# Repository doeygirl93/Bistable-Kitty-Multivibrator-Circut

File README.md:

# Bistable Kitty Multivibrator
###### TOTAL TIME: 3hr 21min
Hackatime: https://lapse.hackclub.com/timelapse/kpVtzk44xacg

This is a PCB for a Bistable multivibrator. I made it cause we were forced to in Reslution hardware week 2. But I choose this spefic circut because I liked how there are only 2 states and it could be useful for many other circuts like analog so I thought this would be a useful on to pratice

DEMO LINKS:
Schematic:
https://kicanvas.org/?repo=https://github.com/doeygirl93/Bistable-Kitty-Multivibrator-Circut/blob/main/src/Kicad/Bistable%20Multivibrator.kicad_sch
PCB:
https://kicanvas.org/?repo=https://github.com/doeygirl93/Bistable-Kitty-Multivibrator-Circut/blob/main/src/Kicad/Bistable%20Multivibrator.kicad_pcb
---

## Simulation

So this works like a flipflop. SO this type of circut only has 2 stable states and it always remains inside on the state until you physically switch to another. And while one is on the other has to be off. In context of digital circuts it can be used as basic memory elements. And i used 6 resitors, 2 led 2 npn transitoris 2 switches.

[Link to Demo]($ 1 0.000005 10.20027730826997 50 5 50 5e-11
R 512 160 480 160 0 0 40 5 0 0 0.5
w 512 160 592 160 0
162 592 256 528 256 2 default-led 1 0 0 0.01
g 528 256 528 272 0 0
w 592 256 592 304 0
t 656 320 592 320 0 1 -0.3882099641741541 0.6902026669380696 100 default
g 592 336 592 384 0 0
w 704 256 816 304 0
w 656 320 816 256 0
w 592 160 912 160 0
162 912 240 992 240 2 default-led 1 0 0 0.01
g 992 240 992 288 0 0
s 656 432 576 432 0 1 false
R 576 432 544 368 0 0 40 5 0 0 0.5
w 912 240 912 288 0
t 880 304 912 304 0 1 -0.38820996417420517 0.6902026669380692 100 default
w 816 304 880 304 0
s 816 416 880 416 0 1 false
R 880 416 880 368 0 0 40 5 0 0 0.5
g 912 320 928 384 0 0
r 592 256 592 160 0 100
r 912 160 912 240 0 100
r 816 256 912 240 0 1000
r 704 256 592 256 0 1000
r 656 320 656 432 0 1000
r 816 304 816 416 0 1000
)

---
## Schematic

## PCB

---

Uhh Thanks to Rohan for helping me for reminding me to do week 2 and teaching me how to fix the Routing my PCB! I was lowk finna give up without it. Also thanks for Rudy for lettting me submit this late😭

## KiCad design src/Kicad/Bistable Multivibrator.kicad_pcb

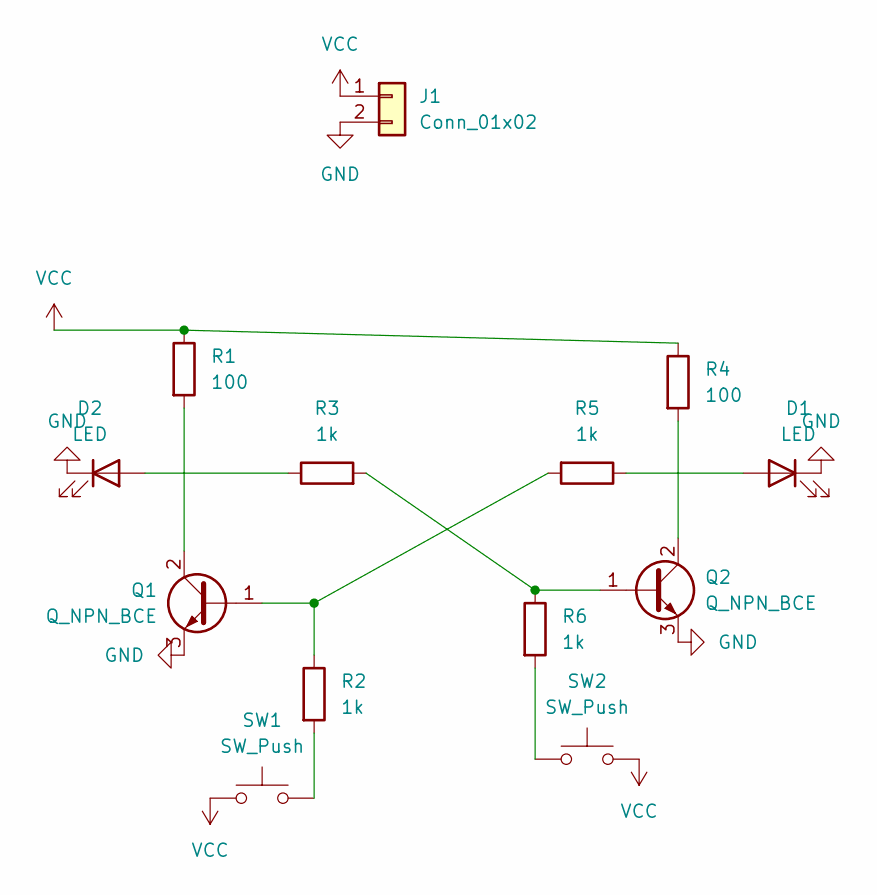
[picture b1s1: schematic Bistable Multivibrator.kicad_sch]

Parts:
D1, D2: LED; LED_D5.0mm
J1: Conn_01x02; PinHeader_1x02_P2.54mm_Vertical
Q1, Q2: Q_NPN_BCE; TO-92L_Inline_Wide
R1, R4: 100; R_Axial_DIN0204_L3.6mm_D1.6mm_P7.62mm_Horizontal
R2, R3, R5, R6: 1k; R_Axial_DIN0204_L3.6mm_D1.6mm_P7.62mm_Horizontal
SW1, SW2: SW_Push; SW_PUSH_6mm

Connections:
GND: D1.1 (K), D2.1 (K), J1.2, Q1.3 (E), Q2.3 (E)
unnamed: D1.2 (A), R5.1
unnamed: D2.2 (A), R3.1
unnamed: Q1.1 (B), R2.1, R5.2
unnamed: Q1.2 (C), R1.2
unnamed: Q2.1 (B), R3.2, R6.1
unnamed: Q2.2 (C), R4.2
unnamed: R2.2, SW1.2
unnamed: R6.2, SW2.1
VCC: J1.1, R1.1, R4.1, SW1.1, SW2.2

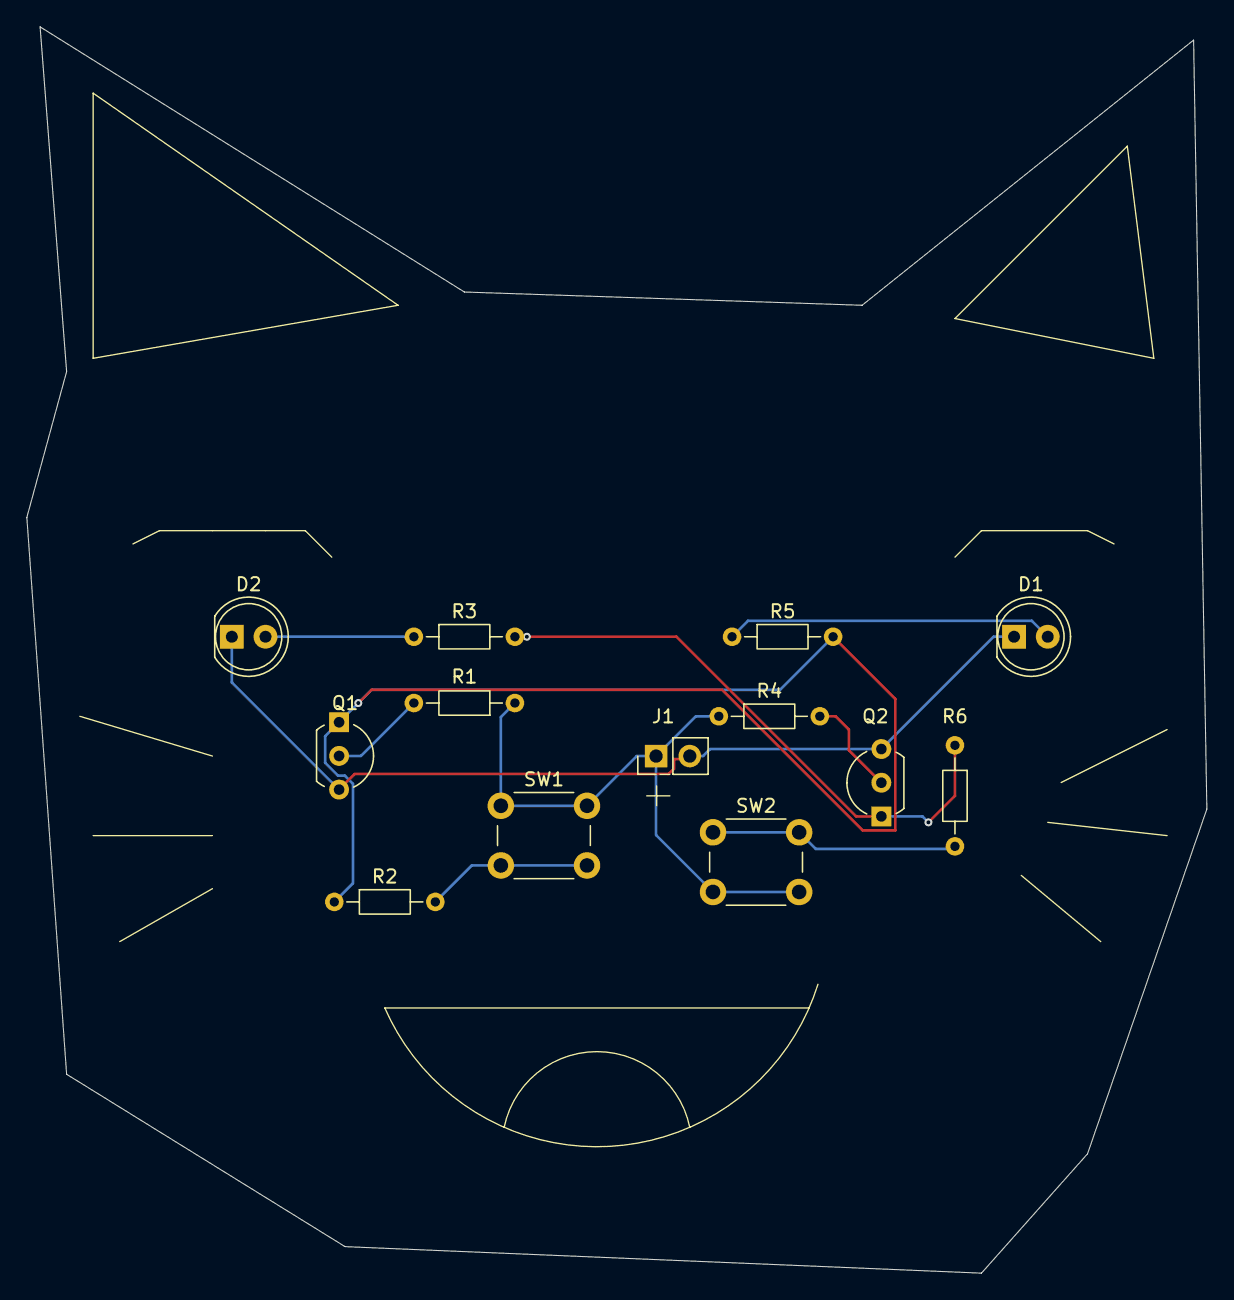
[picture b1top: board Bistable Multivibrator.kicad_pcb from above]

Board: 2 copper layers, 89.0 x 94.0 mm, 13 parts (0 on the bottom side), 10 nets.

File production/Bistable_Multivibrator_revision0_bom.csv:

Designator,Footprint,Quantity,Value,LCSC Part #
"D1, D2",LED_D5.0mm,2,LED,
J1,PinHeader_1x02_P2.54mm_Vertical,1,Conn_01x02,
"Q1, Q2",TO-92L_Inline_Wide,2,Q_NPN_BCE,
"R1, R4",R_Axial_DIN0204_L3.6mm_D1.6mm_P7.62mm_Horizontal,2,100,
"R2, R3, R5, R6",R_Axial_DIN0204_L3.6mm_D1.6mm_P7.62mm_Horizontal,4,1k,
"SW1, SW2",SW_PUSH_6mm,2,SW_Push,

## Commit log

2026-04-08 First commited!
2026-04-08 Added the rest of the files
2026-04-08 Update simulation images and demo link
    Updated images and demo link in README.
2026-04-08 Replace schematic and PCB images with new attachments
    Updated schematic and PCB images in README.
2026-04-08 Update Journal with circuit and PCB design progress
    Added images and detailed progress updates for circuit design, PCB layout, and routing. Documented challenges faced and solutions implemented during the process.
2026-04-08 Add Hackatime link to README
    Added Hackatime link for project time tracking.
2026-04-12 Add demo links to README
    Added demo links for schematic and PCB.
2026-04-12 Document bistable multivibrator circuit progress
    Added detailed journal entries about building a bistable multivibrator circuit, including design, challenges, and PCB layout.
